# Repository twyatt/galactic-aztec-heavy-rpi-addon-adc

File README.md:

# About

Custom Raspberry Pi Add-on ADC board (based on the [Galactic Aztec Raspberry Pi Add-on: Pressure Transducer Interface] board) used to read pressures on the [Galactic Aztec Heavy] rocket. The board has a molex connector for power input (Supply Voltage) and 6 ethernet ports for interfacing with custom [pressure transducer connector boards].

Custom EagleCAD parts on this board can be found in the [SDSU Rocket Eagle Libraries].

## Specifications
| Input | IC      |
|:-----:|:-------:|
| A0    | ADS1114 |
| A1    | ADS1114 |
| A2    | ADS1114 |
| A3    | ADS1114 |
| A4    | ADS1100 |
| A5    | ADS1100 |

### ADS1114
16-bit, 860 SPS ADC

| PGA | Resolution (V) | Maximum Input (V) |
|:---:|:---------------|:-----------------:|
| 2/3 | 0.0001875      | 5.3               |
| 1   | 0.000125       | 4.096             |
| 2   | 0.0000625      | 2.048             |
| 4   | 0.00003125     | 1.024             |
| 8   | 0.000015625    | 0.512             |
| 16  | 0.0000078125   | 0.256             |

### ADS1100
| Bits | Resolution (V) | Sample Rate (SPS) |
|-----:|:---------------|:-----------------:|
| 16   | 0.000152587891 | 8                 |
| 15   | 0.000305175782 | 16                |
| 14   | 0.000610351563 | 32                |
| 12   | 0.00244140625  | 128               |

_Resolution values listed with PGA=1_

## Wiring
The ethernet ports adhere to the following [T-568B] wiring configuration:

| Pin | Color        | Function       |
|:---:|:------------:|:--------------:|
| 1   | Orange/White | Signal         |
| 2   | Orange       | Signal         |
| 3   | Green/White  |                |
| 4   | Blue         | Supply Voltage |
| 5   | Blue/White   | Supply Voltage |
| 6   | Green        |                |
| 7   | Brown/White  | Ground         |
| 8   | Brown        | Ground         |

# Bill of Materials
| Qty | Name  | Description                                    | Notes               | Part Number        | Vendor   |
|:---:|:-----:|------------------------------------------------|---------------------|--------------------|----------|
| 1   | H0    | Header Stacking 2x20 Tall 23mm                 |                     | [1979]             | Adafruit |
| 1   | P0    | Molex Mini Fit Jr. 4-pos Right Angle           |                     | [WM1352-ND]        | DigiKey  |
| 6   | JP0-5 | Jack RJ45 CAT5/CAT5e                           |                     | [380-1046-ND]      | DigiKey  |
| 1   | IC6   | ISO1541 Low-Power Bidirectional I²C Isolator   |                     | [296-34872-1-ND]   | DigiKey  |
| 4   | IC0-3 | ADS1114 16-Bit I²C Analog-to-Digital Converter | Addresses A0-A3     | [296-24932-1-ND]   | DigiKey  |
| 1   | IC4   | ADS1100 16-Bit I²C Analog-to-Digital Converter | Address A4 (100)    | [296-14301-1-ND]   | DigiKey  |
| 1   | IC5   | ADS1100 16-Bit I²C Analog-to-Digital Converter | Address A5 (101)    | [296-14302-1-ND]   | DigiKey  |
| 2   | R0,1  | Resistor 1.8kΩ 1/10W ±1% 0603                  | I²C Pull-up         | [311-1.80KHRCT-ND] | DigiKey  |
| 8   | C0-7  | Capacitor Ceramic 0.1µF ±10% 25V 0603          | Bypass Capacitors   | [490-1524-1-ND]    | DigiKey  |
| 1   | D0    | LED Red Vf=1.8V If=2mA 0603                    | 5V Power Indicator  | [475-1195-2-ND]    | DigiKey  |
| 1   | R2    | Resistor 1.8kΩ 1/4W ±1% 0603                   |                     | [P1.8KBYCT-ND]     | DigiKey  |
| 1   | D1    | LED Yellow Vf=1.8V If=2mA 0603                 | VIN Power Indicator | [475-1196-1-ND]    | DigiKey  |
| 1   | R3    | Resistor 15kΩ 1/4W ±1% 0603                    |                     | [RHM15.0KADCT-ND]  | DigiKey  |

[Galactic Aztec Raspberry Pi Add-on: Pressure Transducer Interface]: https://github.com/twyatt/galactic-aztec-rpi-addon-pressure
[Galactic Aztec Heavy]: http://rocket.sdsu.edu/rockets#galactic-aztec-heavy
[pressure transducer connector boards]: https://github.com/twyatt/galactic-aztec-pressure-transducer-connector
[SDSU Rocket Eagle Libraries]: https://github.com/twyatt/SDSURocket-Eagle-Libraries
[T-568B]: https://en.wikipedia.org/wiki/TIA/EIA-568#Wiring
[1979]: https://www.adafruit.com/product/1979
[WM1352-ND]: http://www.digikey.com/product-detail/en/0039301040/WM1352-ND/561079
[380-1046-ND]: http://www.digikey.com/product-detail/en/SS-7188-NF/380-1046-ND/388308
[296-34872-1-ND]: http://www.digikey.com/product-detail/en/texas-instruments/ISO1541DR/296-34872-1-ND/3587215
[296-24932-1-ND]: http://www.digikey.com/product-detail/en/texas-instruments/ADS1114IDGST/296-24932-1-ND/2123296
[296-14301-1-ND]: http://www.digikey.com/product-detail/en/texas-instruments/ADS1100A4IDBVT/296-14301-1-ND/528555
[296-14302-1-ND]: http://www.digikey.com/product-detail/en/texas-instruments/ADS1100A5IDBVT/296-14302-1-ND/528553
[311-1.80KHRCT-ND]: http://www.digikey.com/product-detail/en/yageo/RC0603FR-071K8L/311-1.80KHRCT-ND/729821
[490-1524-1-ND]: http://www.digikey.com/product-detail/en/murata-electronics-north-america/GRM188R71E104KA01D/490-1524-1-ND/587865
[475-1195-2-ND]: http://www.digikey.com/product-detail/en/LS%20L29K-H1J2-1-Z/475-1195-1-ND/810356
[P1.8KBYCT-ND]: http://www.digikey.com/product-detail/en/ERJ-PA3F1801V/P1.8KBYCT-ND/5036145
[475-1196-1-ND]: http://www.digikey.com/product-detail/en/LY%20L29K-H1K2-26-Z/475-1196-1-ND/810357
[RHM15.0KADCT-ND]: http://www.digikey.com/product-detail/en/rohm-semiconductor/ESR03EZPF1502/RHM15.0KADCT-ND/1983758

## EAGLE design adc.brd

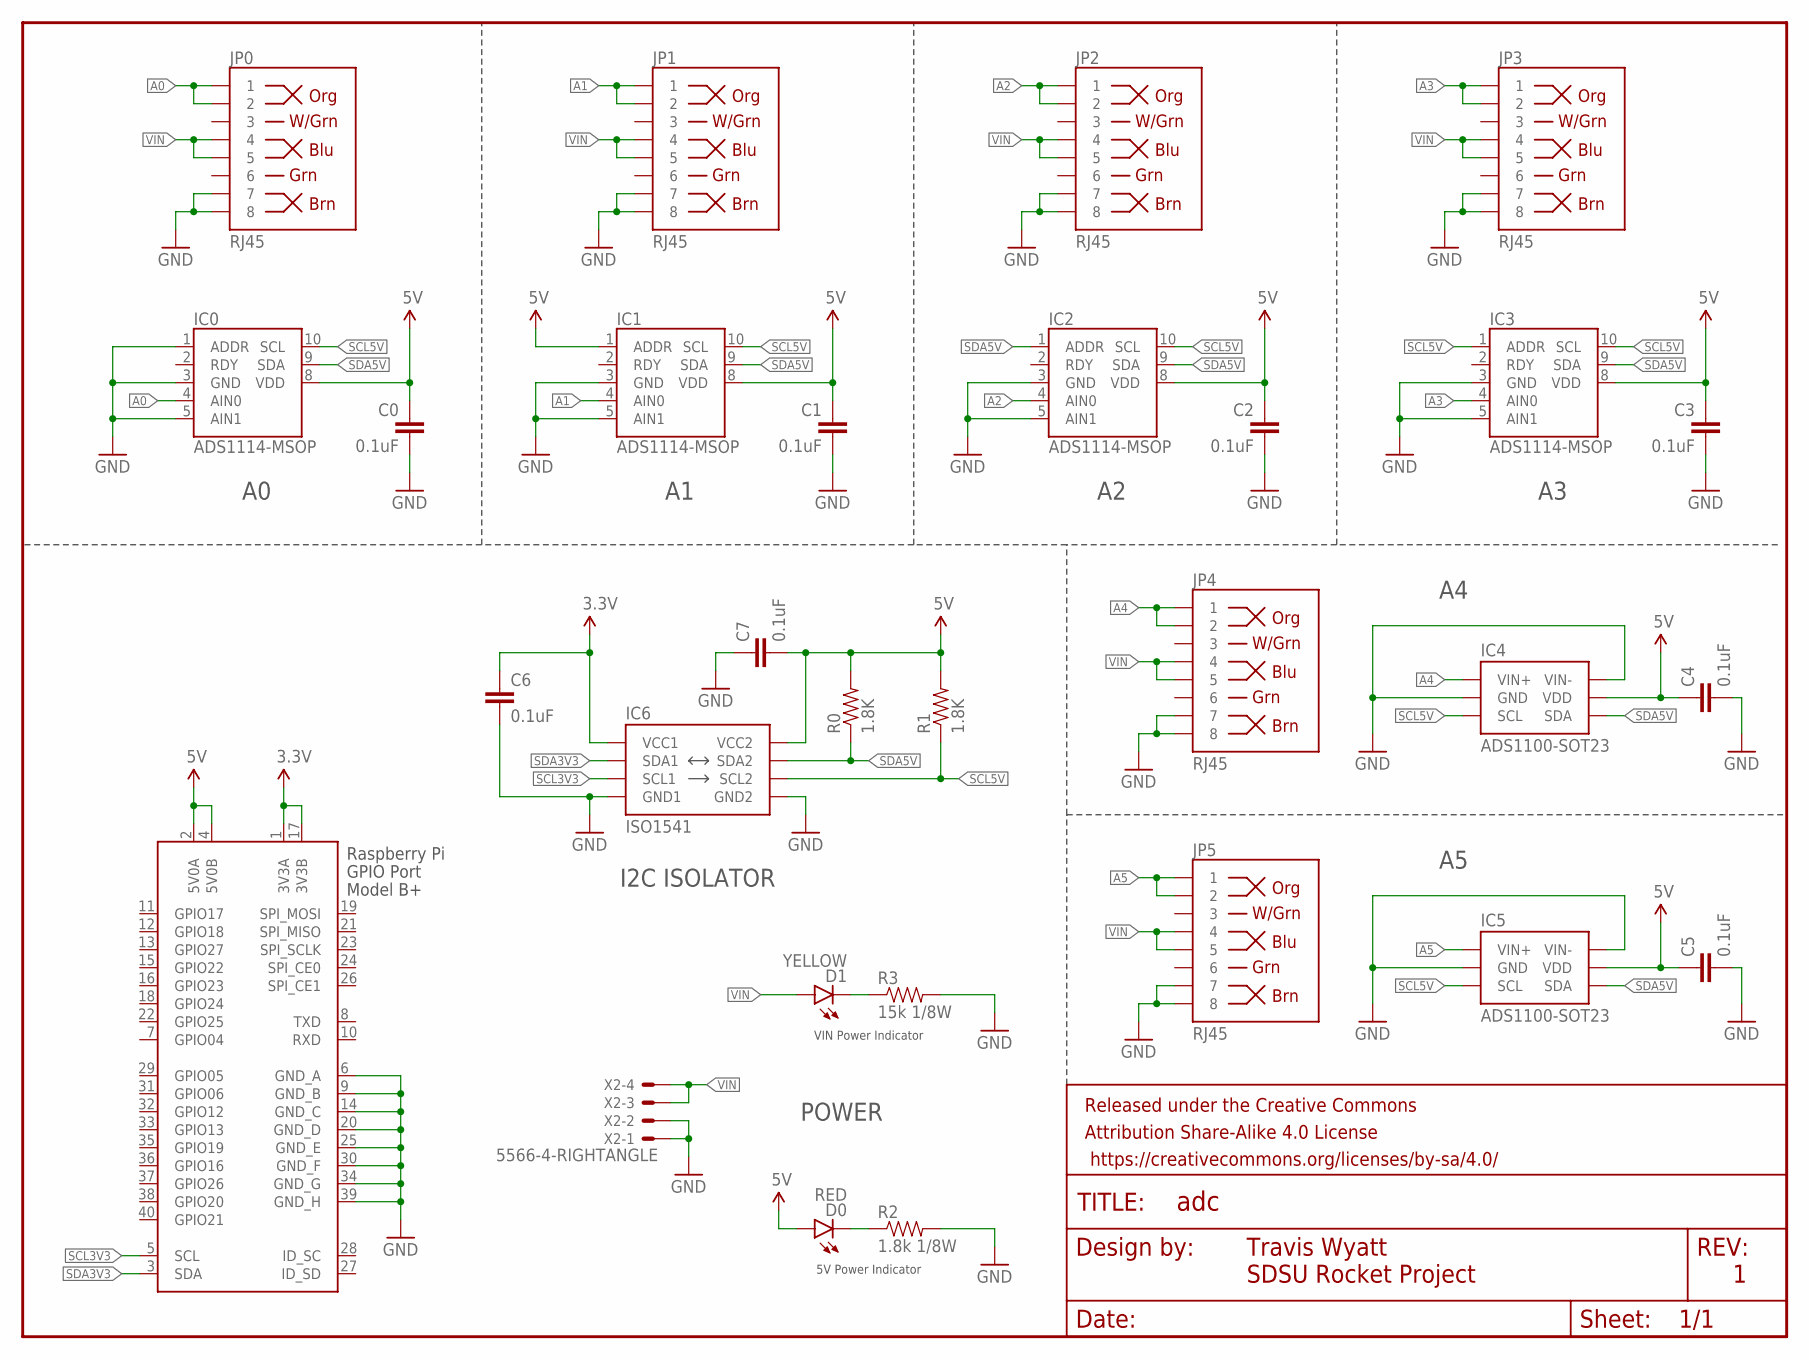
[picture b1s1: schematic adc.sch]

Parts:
C0, C1, C2, C3, C4, C5, C6, C7: 0.1uF; 0603-CAP
D0: RED; LED-0603
D1: YELLOW; LED-0603
FRAME1: FRAME-LETTER; CREATIVE_COMMONS
IC0, IC1, IC2, IC3: ADS1114-MSOP; MSOP10
IC4, IC5: ADS1100-SOT23; SOT23-6
IC6: ISO1541; SOIC8
JP0, JP1, JP2, JP3, JP4, JP5: RJ45; RJ45-8
R0, R1: 1.8K; 0603-RES
R2: 1.8k 1/8W; 0603-RES
R3: 15k 1/8W; 0603-RES
X1: RASPI_BOARD_B+#_H; RASPI_BOARD_B+HAT
X2: 5566-4-RIGHTANGLE; 5566-4

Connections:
3.3V: C6.1, IC6.1 (VCC1), X1.1 (3V3A), X1.17 (3V3B)
5V: C0.1, C1.1, C2.1, C3.1, C4.1, C5.1, C7.2, D0.A, IC0.8 (VDD), IC1.1 (ADDR), IC1.8 (VDD), IC2.8 (VDD), IC3.8 (VDD), IC4.5 (VDD), IC5.5 (VDD), IC6.8 (VCC2), R0.2, R1.2, X1.2 (5V0A), X1.4 (5V0B)
A0: IC0.4 (AIN0), JP0.1, JP0.2
A1: IC1.4 (AIN0), JP1.1, JP1.2
A2: IC2.4 (AIN0), JP2.1, JP2.2
A3: IC3.4 (AIN0), JP3.1, JP3.2
A4: IC4.1 (VIN+), JP4.1, JP4.2
A5: IC5.1 (VIN+), JP5.1, JP5.2
GND: C0.2, C1.2, C2.2, C3.2, C4.2, C5.2, C6.2, C7.1, IC0.1 (ADDR), IC0.3 (GND), IC0.5 (AIN1), IC1.3 (GND), IC1.5 (AIN1), IC2.3 (GND), IC2.5 (AIN1), IC3.3 (GND), IC3.5 (AIN1), IC4.2 (GND), IC4.6 (VIN-), IC5.2 (GND), IC5.6 (VIN-), IC6.4 (GND1), IC6.5 (GND2), JP0.7, JP0.8, JP1.7, JP1.8, JP2.7, JP2.8, JP3.7, JP3.8, JP4.7, JP4.8, JP5.7, JP5.8, R2.2, R3.2, X1.6 (GND_A), X1.9 (GND_B), X1.14 (GND_C), X1.20 (GND_D), X1.25 (GND_E), X1.30 (GND_F), X1.34 (GND_G), X1.39 (GND_H), X2.1, X2.2
unnamed: D1.C, R3.1
unnamed: D0.C, R2.1
SCL3V3: IC6.3 (SCL1), X1.5 (SCL)
SCL5V: IC0.10 (SCL), IC1.10 (SCL), IC2.10 (SCL), IC3.1 (ADDR), IC3.10 (SCL), IC4.3 (SCL), IC5.3 (SCL), IC6.6 (SCL2), R1.1
SDA3V3: IC6.2 (SDA1), X1.3 (SDA)
SDA5V: IC0.9 (SDA), IC1.9 (SDA), IC2.1 (ADDR), IC2.9 (SDA), IC3.9 (SDA), IC4.4 (SDA), IC5.4 (SDA), IC6.7 (SDA2), R0.1
VIN: D1.A, JP0.4, JP0.5, JP1.4, JP1.5, JP2.4, JP2.5, JP3.4, JP3.5, JP4.4, JP4.5, JP5.4, JP5.5, X2.3, X2.4

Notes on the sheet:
Travis Wyatt
SDSU Rocket Project
POWER
5V Power Indicator
VIN Power Indicator
I2C ISOLATOR

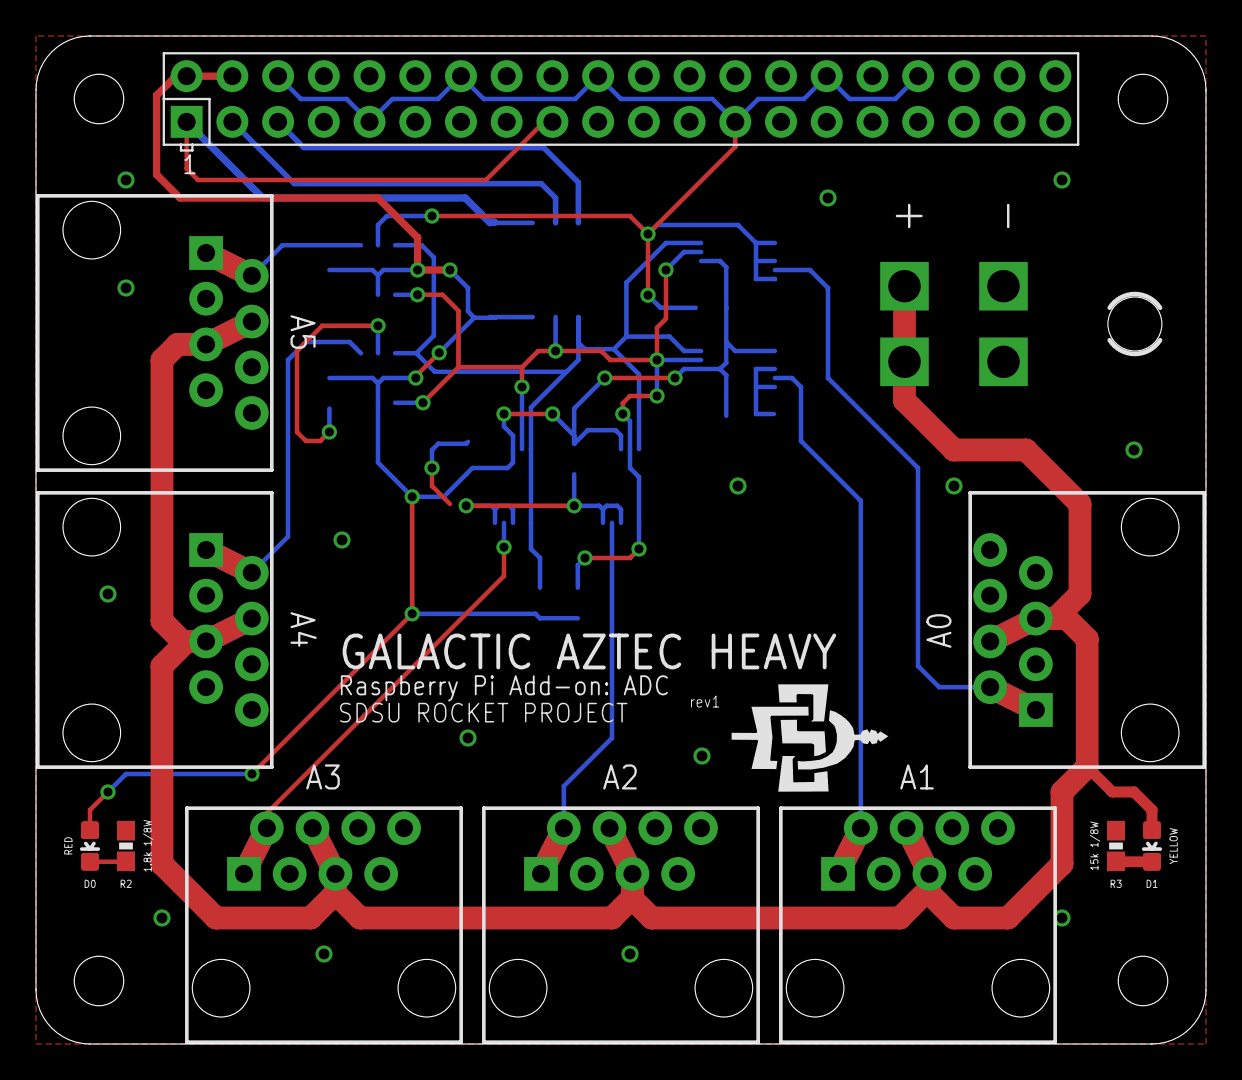
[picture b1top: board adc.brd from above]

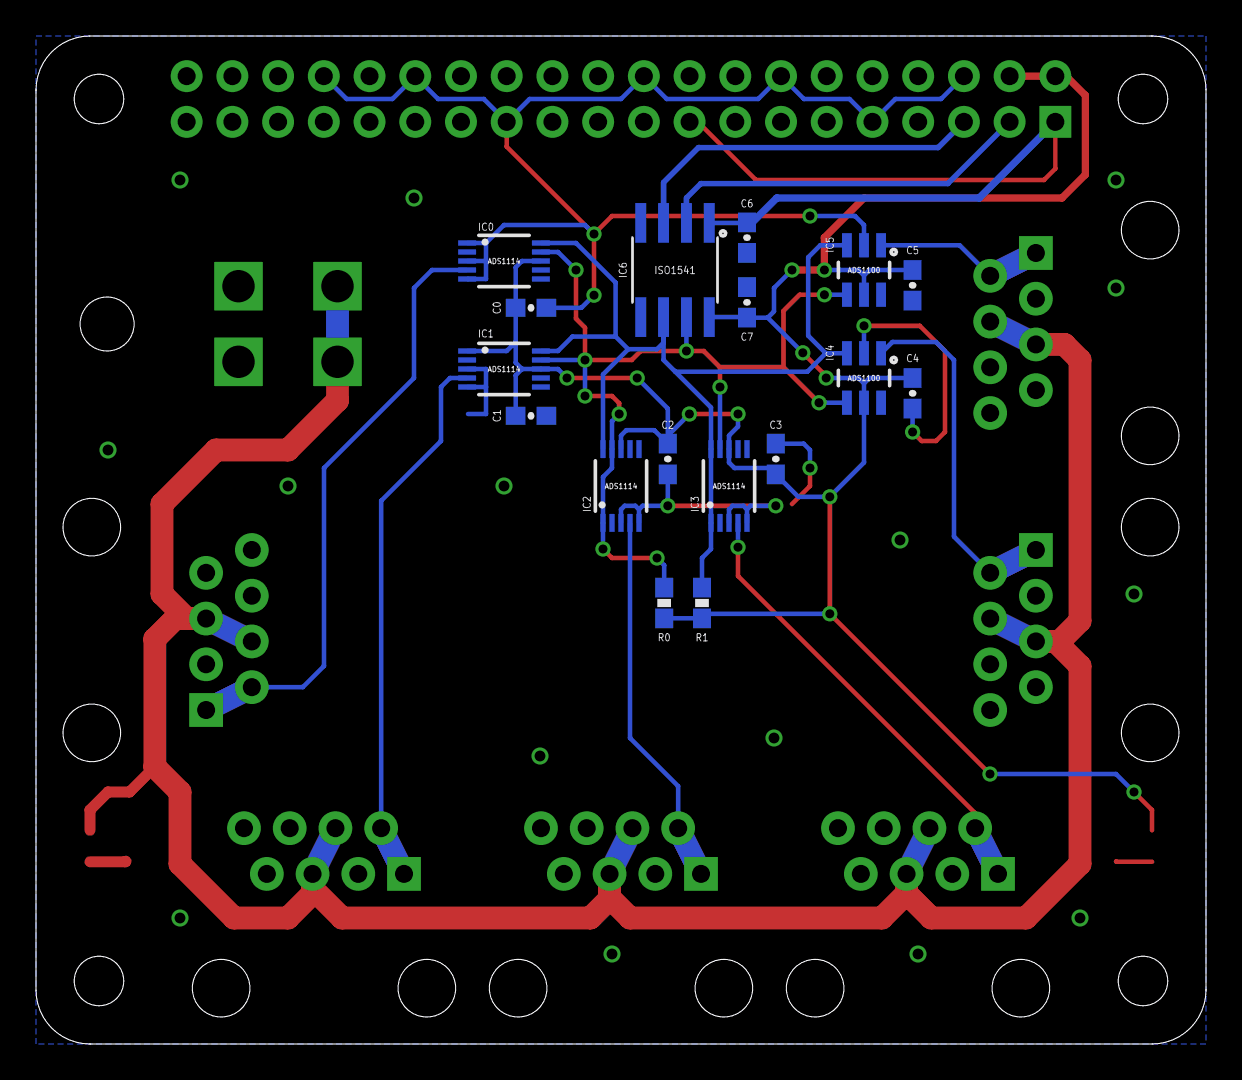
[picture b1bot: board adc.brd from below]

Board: 2 copper layers, 65.0 x 56.0 mm, 30 parts (17 on the bottom side), 16 nets.

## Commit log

2016-03-02 Initial commit
    Created schematic and 2-layer board for Raspberry Pi Add-on: ADC.
2016-03-02 Fix pressure transducer interface link
2016-03-20 Add ADC specifications to readme
2017-04-03 Fix note re: ADS1100 resolution in table

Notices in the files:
parts and their libraries:
SparkFun-Connectors: Licensing: Creative Commons ShareAlike 4.0 International - https://creativecommons.org/licenses/by-sa/4.0
SparkFun-Aesthetics: Released under the Creative Commons Attribution Share-Alike 4.0 License
SparkFun-Aesthetics: https://creativecommons.org/licenses/by-sa/4.0
